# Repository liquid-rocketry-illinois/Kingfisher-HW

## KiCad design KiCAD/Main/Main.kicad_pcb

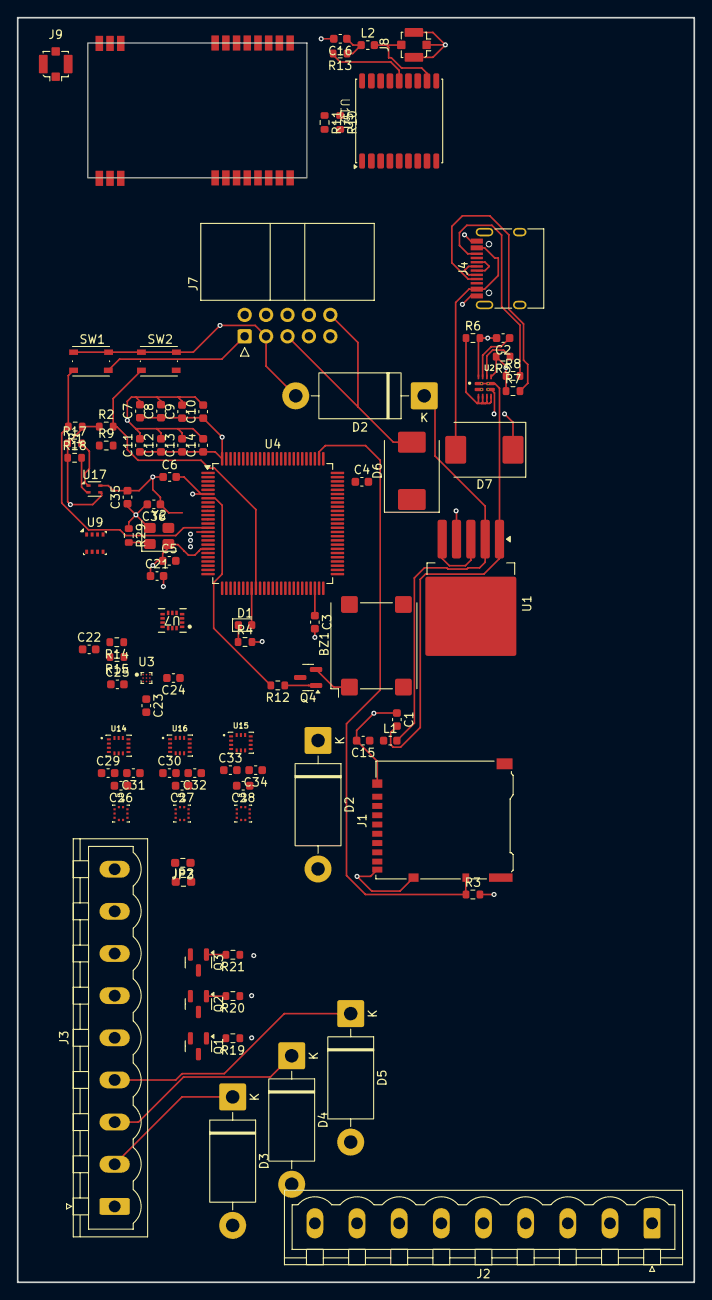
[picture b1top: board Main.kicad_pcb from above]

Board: 4 copper layers, 80.2 x 150.0 mm, 95 parts (0 on the bottom side), 95 nets.

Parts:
BZ1: Buzzer; MagneticBuzzer_PUI_SMT-1028-T-2-R
C1: 680u; C_0603_1608Metric
C2, C16: 10n; C_0603_1608Metric
C3, C4, C23: 2.2u; C_0603_1608Metric
C5: 100N; C_0603_1608Metric
C6, C13: 1u; C_0603_1608Metric
C7, C8, C9, C10, C11, C12, C21, C22, C24, C25, C26, C27, C28, C29, C30, C31, C32, C33, C34, C35: 100n; C_0603_1608Metric
C14: 4.7u; C_0603_1608Metric
C15: 220u; C_0603_1608Metric
C36: 0.1u; C_0603_1608Metric
D1: Green 5mA; LED_0603_1608Metric
D2, D2#2, D3, D4, D5: 1N5820; D_DO-201AD_P15.24mm_Horizontal
D6, D7: MBRS340; D_SMC
J1: Micro_SD_Card_Det2; microSD_HC_Hirose_DM3AT-SF-PEJM5
J2, J3: Screw_Terminal_01x09; PhoenixContact_MSTBVA_2,5_9-G_1x09_P5.00mm_Vertical
J4: USB_C_Receptacle_USB2.0_16P; USB_C_Receptacle_HRO_TYPE-C-31-M-12
J7: Conn_02x05_Top_Bottom_MountingPin; IDC-Header_2x05_P2.54mm_Horizontal
J8, J9: Conn_Coaxial; U.FL_Molex_MCRF_73412-0110_Vertical
JP2: BMI270 TMR Toggle; R_0603_1608Metric_Pad0.98x0.95mm_HandSolder
JP3: BMP390 TMR Toggle; R_0603_1608Metric_Pad0.98x0.95mm_HandSolder
L1: 33u; L_0603_1608Metric
L2: 47n; L_0603_1608Metric
Q1, Q2, Q3: AO3400A; SOT-23
Q4: 2N7002; SOT-23
R1: 10K; R_0603_1608Metric
R2: 100K; R_0603_1608Metric
R3, R5: 100k; R_0603_1608Metric
R4: 634; R_0603_1608Metric
R6, R13: 10; R_0603_1608Metric
R7, R8: 5.1k; R_0603_1608Metric
R9, R14, R15, R17, R18, R19, R20, R21: 10k; R_0603_1608Metric
R10, R11: 47; R_0603_1608Metric
R12: 100; R_0603_1608Metric
R29: 1k; R_0603_1608Metric
SW1: RESET; SW_Push_1P1T_NO_Vertical_Wuerth_434133025816
SW2: USER; SW_Push_1P1T_NO_Vertical_Wuerth_434133025816
U1: LM2596S-3.3; TO-263-5_TabPin3
U2: TPS2121RUXR; IC_TPS2121RUXR
U3: BMM350; BGA9C40P3X3_128X128X50
U4: STM32H750VBTx; LQFP-100_14x14mm_P0.5mm
U5: MAX-M8Q; ublox_MAX
U7: ISM6HG256x; U_LGA-14L_2p5X3p0X0p83_STM
U9: BME280; Bosch_LGA-8_2.5x2.5mm_P0.65mm_ClockwisePinNumbering
U10: E22-900T22S
U11, U12, U13: BMP390L; XDCR_BMP390L
U14, U15, U16: BMI270; XDCR_BMI270
U17: SHT4x; Sensirion_DFN-4_1.5x1.5mm_P0.8mm_SHT4x_NoCentralPad
Y2: SiT8008xx-2x-xxE (25MHz); Oscillator_SMD_SiT_PQFN-4Pin_3.2x2.5mm

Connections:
+3V3: BZ1.2 (-), C6.2, C7.1, C8.1, C9.1, C10.1, C11.1, C12.1, C13.1, C14.1, C15.1, C21.2, C22.2, C24.2, C25.2, C26.1, C31.1, C35.1, C36.2, J1.4 (VDD), J3.1 (3V3_OUT), J7.4, J7.9, JP2.2 (B), JP3.2 (B), L1.1, R1.1, R2.1, R3.2, R14.2, R15.2, R17.1, R18.1, R29.1, U1.4 (FB), U3.B3 (VDDIO), U3.C1 (VDD), U4.6 (VBAT), U4.11 (VDD), U4.21 (VDDA), U4.27 (VDD), U4.50 (VDD), U4.75 (VDD), U4.100 (VDD), U5.6 (V_BCKP), U5.7 (VCC_IO), U5.8 (VCC), U5.13 (LNA_EN), U7.5 (VDDIO), U7.8 (VDD), U9.2 (CSB), U9.6 (VDDIO), U9.8 (VDD), U10.8 (VCC), U11.1 (VDDIO), U11.10 (VDD), U14.8 (VDD), U17.3 (VDD), Y2.4 (Vdd)
+5V: D6.1 (K), D7.1 (K), U2.7 (IN1), U2.7_1 (IN1)
/Barometer/BMP390 INT1: U4.1 (PE2), U11.7 (INT/DNC)
/Barometer/BMP390 INT2: U4.2 (PE3), U12.7 (INT/DNC)
/Barometer/BMP390 INT3: U4.3 (PE4), U13.7 (INT/DNC)
/Barometer/BMP390_CS1: U4.55 (PD8), U11.6 (~CS)
/Barometer/BMP390_CS2: U4.56 (PD9), U12.6 (~CS)
/Barometer/BMP390_CS3: U4.57 (PD10), U13.6 (~CS)
/Barometer/BMP390_MISO: U4.43 (PE13), U11.5 (SDO/DNC/SA0), U12.5 (SDO/DNC/SA0), U13.5 (SDO/DNC/SA0)
/Barometer/BMP390_MOSI: U4.44 (PE14), U11.4 (SDI/SDO/SDA), U12.4 (SDI/SDO/SDA), U13.4 (SDI/SDO/SDA)
/Barometer/BMP390_SCK: U4.42 (PE12), U11.2 (SCK/SCL), U12.2 (SCK/SCL), U13.2 (SCK/SCL)
/GPS/GPS_RESET: U4.24 (PA2), U5.9 (~RESET)
/GPS/GPS_SCL: R11.2, U4.59 (PD12)
/GPS/GPS_SDA: R10.2, U4.60 (PD13)
/IMUs/BNO_CS: U4.51 (PB12), U7.12 (CS)
/IMUs/BNO_INT: U4.65 (PC8), U7.4 (INT1)
/IMUs/BNO_MISO: U4.53 (PB14), U7.1 (SDO/TA0)
/IMUs/BNO_MOSI: U4.54 (PB15), U7.2 (SDx)
/IMUs/BNO_SCK: U4.52 (PB13), U7.3 (SCx)
/Microcontroller/DEBUG_JTMS-SWCLK: J7.6, U4.76 (PA14)
/Microcontroller/DEBUG_JTMS-SWDIO: J7.7, U4.72 (PA13)
/Microcontroller/Drogue Eject Backup: R20.1, U4.16 (PC1)
/Microcontroller/Drogue Eject Main: R19.1, U4.15 (PC0)
/Microcontroller/Main Eject: R21.1, U4.17 (PC2_C)
/Microcontroller/Radio AUX: U4.80 (PC12), U10.6 (AUX)
/Microcontroller/Radio RST: U4.81 (PD0), U10.7 (RST)
/Microcontroller/Radio RX: U4.95 (PB8), U10.3 (TXD)
/Microcontroller/Radio TX: U4.78 (PC10), U10.2 (RXD)
/Microcontroller/SD CS: J1.2 (DAT3/CD), U4.28 (PA4)
/Microcontroller/SD MOSI: J1.3 (CMD), U4.31 (PA7)
/Microcontroller/SD_CLK: J1.5 (CLK), U4.29 (PA5)
/Microcontroller/SD_Det: J1.10 (DET_A), R3.1, U4.77 (PA15)
/Microcontroller/SD_MISO: J1.7 (DAT0), U4.90 (PB4)
/Microcontroller/SHT41 SCL: R18.2, U4.46 (PB10), U17.2 (SCL)
/Microcontroller/SHT41 SDA: R17.2, U4.47 (PB11), U17.1 (SDA)
/Microcontroller/SIMU1 INT: U4.69 (PA10), U14.4 (INT1)
/Microcontroller/SIMU2 INT: U4.68 (PA9), U15.4 (INT1)
/Microcontroller/SIMU3 INT: U4.67 (PA8), U16.4 (INT1)
/Microcontroller/SIMU CLK: U4.89 (PB3), U14.13 (SCX), U15.13 (SCX), U16.13 (SCX)
/Microcontroller/SIMU CS1: U4.37 (PE7), U14.12 (CSB)
/Microcontroller/SIMU CS2: U4.38 (PE8), U15.12 (CSB)
/Microcontroller/SIMU CS3: U4.35 (PB1), U16.12 (CSB)
/Microcontroller/SIMU MISO: U4.79 (PC11), U14.1 (SDO), U15.1 (SDO), U16.1 (SDO)
/Microcontroller/SIMU MOSI: U4.36 (PB2), U14.14 (SDX), U15.14 (SDX), U16.14 (SDX)
/Microcontroller/Servo1_DOut: J2.3 (Servo1), U4.82 (PD1)
/Microcontroller/Servo1_Encoder: J2.5 (Servo1_Encoder), U4.84 (PD3)
/Microcontroller/Servo2_DOut: J2.4 (Servo2), U4.83 (PD2)
/Microcontroller/Servo2_Encoder: J2.6 (Servo2_Encoder), U4.85 (PD4)
/Microcontroller/USBC_D+: J4.A6 (D+), J4.B6 (D+), U4.71 (PA12)
/Microcontroller/USBC_D-: J4.A7 (D-), J4.B7 (D-), U4.70 (PA11)
/Microcontroller/USER_BTN: R2.2, SW2.2, U4.34 (PB0)
/Microcontroller/USER_LED: D1.2 (A), U4.33 (PC5)
/Microcontroller/~OSC_OUT: U4.12 (PH0), Y2.3 (OUT)
/~RESET: J7.1, R1.2, SW1.2, U4.14 (NRST)
GND: C1.1, C2.2, C3.2, C4.2, C5.1, C6.1, C7.2, C8.2, C9.2, C10.2, C11.2, C12.2, C13.2, C14.2, C15.2, C16.2, C21.1, C22.1, C23.2, C24.1, C25.1, C26.2, C27.2, C28.2, C29.2, C30.2, C31.2, C32.2, C33.2, C34.2, C35.2, C36.1, D2.2 (A), D2#2.2 (A), J1.6 (VSS), J1.9 (DET_B), J1.11 (SHIELD), J2.2 (GND), J2.7 (MotorGND), J3.8, J3.9 (GND), J4.A1 (GND), J4.A12 (GND), J4.B1 (GND), J4.B12 (GND), J7.3, J7.8, J8.2 (Ext), J9.2 (Ext), Q1.3 (D), Q2.3 (D), Q3.3 (D), Q4.3 (D), R4.2, R5.2, R6.2, R7.1, R8.1, R9.1, SW1.1, SW2.1, U1.3 (GND), U1.5 (~ON/OFF), U2.9 (ST), U2.12 (GND), U3.B1 (GND), U3.B2 (ADSEL), U3.C3 (BYPASS), U4.10 (VSS), U4.19 (VSSA), U4.26 (VSS), U4.49 (VSS), U4.74 (VSS), U4.99 (VSS), U5.1 (GND), U5.10 (GND), U5.12 (GND), U7.6 (GND), U9.1 (GND), U9.7 (GND), U10.4 (M0), U10.5 (M1), U11.3 (VSS/GND), U11.8 (VSS/GND), U11.9 (VSS/GND), U12.3 (VSS/GND), U12.8 (VSS/GND), U12.9 (VSS/GND), U13.3 (VSS/GND), U13.8 (VSS/GND), U13.9 (VSS/GND), U14.6 (GNDIO), U14.7 (GND), U15.6 (GNDIO), U15.7 (GND), U16.6 (GNDIO), U16.7 (GND), U17.4 (VSS), Y2.2 (GND)
unnamed: BZ1.1 (+), Q4.2 (S)
unnamed: C3.1, U4.48 (VCAP)
unnamed: C4.1, U4.73 (VCAP)
unnamed: C16.1, L2.1, R13.1
unnamed: D1.1 (K), R4.1
unnamed: D2.1 (K), D2#2.1 (K), L1.2, U1.2 (OUT)
unnamed: D3.2 (A), D4.2 (A), D5.2 (A), J2.1 (7.4V_IN), J2.8 (MotorPwr1), J2.9 (MotorPwr2), U2.2 (IN2), U2.2_1 (IN2)
unnamed: D3.1 (K), J3.2 (Pyro_OUT_1)
unnamed: D4.1 (K), J3.3 (Pyro_OUT_2)
unnamed: D5.1 (K), J3.4 (Pyro_OUT_3)
unnamed: D6.2 (A), J7.5, J7.10
unnamed: D7.2 (A), J4.A4 (VBUS), J4.A9 (VBUS), J4.B4 (VBUS), J4.B9 (VBUS)
unnamed: J3.6 (Drogue_Backup), Q2.2 (S)
unnamed: J3.5 (Drogue_Main), Q1.2 (S)
unnamed: J3.7 (Main_Parachute), Q3.2 (S)
unnamed: J4.A5 (CC1), R7.2
unnamed: J4.B5 (CC2), R8.2
unnamed: J8.1 (In), L2.2, U5.11 (RF_IN)
unnamed: J9.1 (In), U10.1 (ANT)
unnamed: C30.1, C32.1, C33.1, C34.1, JP2.1 (A), U15.5 (VDDIO), U15.8 (VDD), U16.5 (VDDIO), U16.8 (VDD)
unnamed: C27.1, C28.1, JP3.1 (A), U12.1 (VDDIO), U12.10 (VDD), U13.1 (VDDIO), U13.10 (VDD)
unnamed: Q1.1 (G), R19.2
unnamed: Q2.1 (G), R20.2
unnamed: Q3.1 (G), R21.2
unnamed: Q4.1 (G), R12.1
unnamed: C1.2, U1.1 (VIN), U2.1 (OUT), U2.1_1 (OUT), U2.8 (OUT), U2.8_1 (OUT)
unnamed: R6.1, U2.3 (CP2), U2.4 (OV2), U2.5 (OV1), U2.6 (PR1)
unnamed: R5.1, U2.10 (ILIM)
unnamed: C2.1, U2.11 (SS)
unnamed: C23.1, U3.C2 (CRST)
unnamed: R14.1, U3.A3 (SCK), U7.10 (OCS_Aux)
unnamed: R15.1, U3.A2 (SDA), U7.11 (SDO_Aux)
unnamed: R9.2, U4.94 (BOOT0)
unnamed: R12.2, U4.7 (PC13)
unnamed: C5.2, U4.20 (VREF+)
unnamed: R11.1, U5.17 (SCL)
unnamed: R10.1, U5.16 (SDA)
unnamed: R13.2, U5.14 (VCC_RF)
unnamed: C29.1, U14.5 (VDDIO)
unnamed: R29.2, Y2.1 (OE)

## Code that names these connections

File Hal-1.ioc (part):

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Mcu.Name=STM32H750VBTx
Mcu.Package=LQFP100
Mcu.UserName=STM32H750VBTx
PA10.GPIOParameters=GPIO_Label
PA10.GPIO_Label=SIMU1 INT
PA10.Signal=GPIO_Input
PA11.GPIOParameters=GPIO_Label
PA11.GPIO_Label=USB D-
PA11.Signal=USB_OTG_FS_DM
PA12.GPIOParameters=GPIO_Label
PA12.GPIO_Label=USB D+
PA12.Signal=USB_OTG_FS_DP
PA13\ (JTMS/SWDIO).Signal=DEBUG_JTMS-SWDIO
PA14\ (JTCK/SWCLK).Signal=DEBUG_JTCK-SWCLK
PA15\ (JTDI).GPIOParameters=GPIO_Label
PA15\ (JTDI).GPIO_Label=SD_Det
PA15\ (JTDI).Signal=GPIO_Input
PA2.GPIOParameters=GPIO_Label
PA2.GPIO_Label=RESET [GPS]
PA2.Signal=GPIO_Output
PA4.GPIOParameters=GPIO_Label
PA4.GPIO_Label=CS1 [SD Card]
PA4.Signal=SPI1_NSS
PA5.GPIOParameters=GPIO_Label
PA5.GPIO_Label=SCK1 [SD Card]
PA5.Signal=SPI1_SCK
PA7.GPIOParameters=GPIO_Label
PA7.GPIO_Label=MOSI1 [SD Card]
PA7.Signal=SPI1_MOSI
PA8.GPIOParameters=GPIO_Label
PA8.GPIO_Label=SIMU3 INT
PA8.Signal=GPIO_Input
PA9.GPIOParameters=GPIO_Label
PA9.GPIO_Label=SIMU2 INT
PA9.Signal=GPIO_Input
PB0.GPIOParameters=GPIO_Label
PB0.GPIO_Label=User BTN
PB0.Signal=GPIO_Output
PB1.GPIOParameters=GPIO_Label
PB1.GPIO_Label=CS3 [SIMUs]
PB1.Signal=GPIO_Output
PB10.GPIOParameters=GPIO_Label
PB10.GPIO_Label=SHT41 SCL
PB10.Signal=I2C2_SCL
PB11.GPIOParameters=GPIO_Label
PB11.GPIO_Label=SHT41 SDA
PB11.Signal=I2C2_SDA
PB12.GPIOParameters=GPIO_Label
PB12.GPIO_Label=CS [ISM]
PB12.Signal=GPIO_Output
PB13.GPIOParameters=GPIO_Label
PB13.GPIO_Label=SCK2 [ISM]
PB13.Signal=SPI2_SCK
PB14.GPIOParameters=GPIO_Label
PB14.GPIO_Label=MISO2 [ISM]
PB14.Signal=SPI2_MISO
PB15.GPIOParameters=GPIO_Label
PB15.GPIO_Label=MOSI2 [ISM]
PB15.Signal=SPI2_MOSI
PB2.GPIOParameters=GPIO_Label
PB2.GPIO_Label=SPI3 MOSI [SIMUs]
PB2.Signal=SPI3_MOSI
PB3\ (JTDO/TRACESWO).GPIOParameters=GPIO_Label
PB3\ (JTDO/TRACESWO).GPIO_Label=SPI3 CLK [SIMUs]
PB3\ (JTDO/TRACESWO).Signal=SPI3_SCK
PB4\ (NJTRST).GPIOParameters=GPIO_Label
PB4\ (NJTRST).GPIO_Label=MISO1 [SD Card]
PB4\ (NJTRST).Signal=SPI1_MISO
PB8.GPIOParameters=GPIO_Label
PB8.GPIO_Label=Radio RX
PB8.Signal=UART4_RX
PC0.GPIOParameters=GPIO_Label
PC0.GPIO_Label=Drogue Main Pyro
PC0.Signal=GPIO_Output
PC1.GPIOParameters=GPIO_Label
PC1.GPIO_Label=Drogue Backup Pyro
PC1.Signal=GPIO_Output
PC10.GPIOParameters=GPIO_Label
PC10.GPIO_Label=Radio TX
PC10.Signal=UART4_TX
PC11.GPIOParameters=GPIO_Label
PC11.GPIO_Label=SPI3 MISO [SIMUs]
PC11.Signal=SPI3_MISO
PC12.GPIOParameters=GPIO_Label
PC12.GPIO_Label=Radio AUX
PC12.Signal=GPIO_Input
PC13.GPIOParameters=GPIO_Label
PC13.GPIO_Label=BUZZER_OUT
PC13.Signal=GPIO_Analog
PC2_C.GPIOParameters=GPIO_Label
PC2_C.GPIO_Label=Primary Parachute Pyro
PC2_C.Signal=GPIO_Output
PC5.GPIOParameters=GPIO_Label
PC5.GPIO_Label=User LED
PC5.Signal=GPIO_Output
PC8.GPIOParameters=GPIO_Label
PC8.GPIO_Label=ISM INT
PC8.Signal=GPIO_Output
PD0.GPIOParameters=GPIO_Label
PD0.GPIO_Label=RST [Radio]
PD0.Signal=GPIO_Output
PD1.GPIOParameters=GPIO_Label
PD1.GPIO_Label=Servo1_DOut
PD1.Signal=GPIO_Output
PD10.GPIOParameters=GPIO_Label
PD10.GPIO_Label=CS3 [BMP390]
PD10.Signal=GPIO_Output
PD12.GPIOParameters=GPIO_Label
PD12.GPIO_Label=GPS I2CSCL
PD12.Signal=I2C4_SCL
PD13.GPIOParameters=GPIO_Label
PD13.GPIO_Label=GPS I2CSDA
PD13.Signal=I2C4_SDA
PD2.GPIOParameters=GPIO_Label
PD2.GPIO_Label=Servo2_DOut
PD2.Signal=GPIO_Output
PD3.GPIOParameters=GPIO_Label
PD3.GPIO_Label=Servo1_Encoder
PD3.Signal=GPIO_Input
PD4.GPIOParameters=GPIO_Label
PD4.GPIO_Label=Servo2_Encoder
PD4.Signal=GPIO_Input
PD8.GPIOParameters=GPIO_Label
PD8.GPIO_Label=CS1 [BMP390]
PD8.Signal=GPIO_Output
PD9.GPIOParameters=GPIO_Label
PD9.GPIO_Label=CS2 [BMP390]
PD9.Signal=GPIO_Output
PE10.GPIOParameters=GPIO_Label
PE10.GPIO_Label=CS2 [SHT41]
PE10.Signal=GPIO_Output
PE11.GPIOParameters=GPIO_Label
PE11.GPIO_Label=CS3 [SHT41]
PE11.Signal=GPIO_Output
PE12.GPIOParameters=GPIO_Label
PE12.GPIO_Label=SCK4 [BMP390]
PE12.Signal=SPI4_SCK
PE13.GPIOParameters=GPIO_Label
PE13.GPIO_Label=MISO4 [BMP390]
PE13.Signal=SPI4_MISO
PE14.GPIOParameters=GPIO_Label
PE14.GPIO_Label=MOSI4 [BMP390]
PE14.Signal=SPI4_MOSI
PE2.GPIOParameters=GPIO_Label
PE2.GPIO_Label=BMP390 INT1
PE2.Signal=GPIO_Input
PE3.GPIOParameters=GPIO_Label
PE3.GPIO_Label=BMP390 INT2
PE3.Signal=GPIO_Input
PE4.GPIOParameters=GPIO_Label
PE4.GPIO_Label=BMP390 INT3
PE4.Signal=GPIO_Input
PE7.GPIOParameters=GPIO_Label
PE7.GPIO_Label=CS1 [SIMUs]
PE7.Signal=GPIO_Output
PE8.GPIOParameters=GPIO_Label
PE8.GPIO_Label=CS2 [SIMUs]
PE8.Signal=GPIO_Output
PE9.GPIOParameters=GPIO_Label
PE9.GPIO_Label=CS1 [SHT41]
PE9.Signal=GPIO_Output
PH0-OSC_IN\ (PH0).Signal=RCC_OSC_IN
RCC.SYSCLKFreq_VALUE=64000000
board=custom

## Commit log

2025-10-14 Add blank Kicad files
2025-10-14 Basic PWR systems
2025-10-18 Update power modules
2025-10-21 Incr change to mcu
2025-10-27 wip camera pin allocations (consult link on Slack)
2025-10-27 Update MCU to display connections
2025-11-04 add imu_sensor sch
2025-11-05 Complete GPS section
2025-11-05 Fix labeling issue
2025-11-05 Add pin assignments for other sensors
2025-11-07 replace previous imu folder with one that doesn't produce git errors
2025-11-11 Continue integrating
2025-11-11 add baro
2025-11-18 Stable update. Begin fixing previous commit errors
2025-11-18 Add new rf
2025-11-18 post meeting update
2025-11-21 Remove thermocouples due to complexity and focus switch
2025-11-27 prep for merge
2025-11-27 remove random lock file
2025-11-27 Keep up to date
2025-11-28 Add datasheets and revise TMR goals
2025-12-02 Polish for review
2025-12-15 Create wiring diagram draft
2025-12-15 Update wiring diagram with TM input
2025-12-20 Submit design for review
2025-12-23 Update RF sys and footprints
2025-12-26 Begin PCB layout
